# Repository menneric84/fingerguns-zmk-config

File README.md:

# v1.1
v1.1 includes support for one ALPS EC12 rotary encoder that can be placed in either the right or the left corner.  Both sockets are wired to the same pins (gpio 0 and gpio 1), so only one can be used at a time.

Pinout is identical, but the ZMK repo is not currently configured for rotary encoders.  I will dive into rotary encoders in ZMK when I have time.

Other changes: moved MCU closer to the edge, rotated hotswaps on col10 (the 11th column) to make design of the 10col case easier.

# ZMK
YOU MUST CHECK rick-plank.overlay TO ENSURE THE PROPER PHYSICAL LAYOUT IS CHOSEN

Please see the comments on line 4 of rick-plank.overlay.  In the 'chosen' node, you will need to adjust zmk,physical-layout depending on if you are using the 12 column variant or the 10 column variant of the Rick Plank PCB.

The 12 column is represented by &layout_12col
The 10 column is represented by &layout_10col

YOU MUST SELECT OR CREATE AN APPROPRIATE KEYMAP

In the ergomech community a keymap is an intensely personal thing.  That being said, I've included my own 12 column and 10 column keymaps in case you need somewhere to start.  Please note that rick-plank.keymap is intended for the 10 column variant.  A 12 column keymap is also included under the name rick-plank.keymap.12col.  If you wish to use 12 columns, simply append '.10col' to the default keymap and delete '.12col' from the other one.

# QMK?
I haven't tried it, but there's no reason it wouldn't work fine.  You'll find the pinout in the kicad schematic.  Please reach out and let me know how it goes!  If you get it up and running I'd be happy to add a QMK option to the repo.

# BOM
36-42 choc switches & keycaps  
36-42 choc hotswaps  
36-42 smd diodes  
6 M2 heat set inserts  
6 M2 x 6mm screws  
6 rubber bumpons (recommended)  
1 MSK12C02 switch  
1 Panasonic EVQPUJ_EVQPUA button  
1 pro micro form factor MCU  
1 301230 110mAh battery (optional)  

If you are confused about switches, all parts except the inserts and screws can be sourced from typeractive.xyz.

# BUILDING

If planning to use the case, the MCU should be soldered with the included headers, NOT sockets.  The sockets add too much height to fit in the case.  A hot plate is recommended for assembly, as it makes the whole process very quick and easy.  Assembly is possible by hand with a soldering iron, though it can be delicate and frustrating.  For the diodes and switches, I recommend tinning one pad first, then placing the component with tweezers before soldering the other side.  Some of the photos show a battery pigtail, but ultimately I decided to solder the battery wires directly to the board and stick the battery down with a command strip.

# CASES

Files are included to 3d print a case for the 12col variant, designed by my brother.  PCB is secured with 6 M2 heat set inserts. The 10col case is still in development, but will be added to the repo when it's done.  I've also included a .step file of the PCB under /gerbers_and_kicad if you'd like to design your own.

Rick Plank is also perfectly useable without a case if you stick a few bumpons on the hotswaps.  I placed a total of six, at the four corners and at the corners of the bottom row.

# LICENSING
All hardware in this repo is licensed under CERN-OHL-S-2.0, available at https://gitlab.com/ohwr/project/cernohl/-/wikis/uploads/819d71bea3458f71fba6cf4fb0f2de6b/cern_ohl_s_v2.txt

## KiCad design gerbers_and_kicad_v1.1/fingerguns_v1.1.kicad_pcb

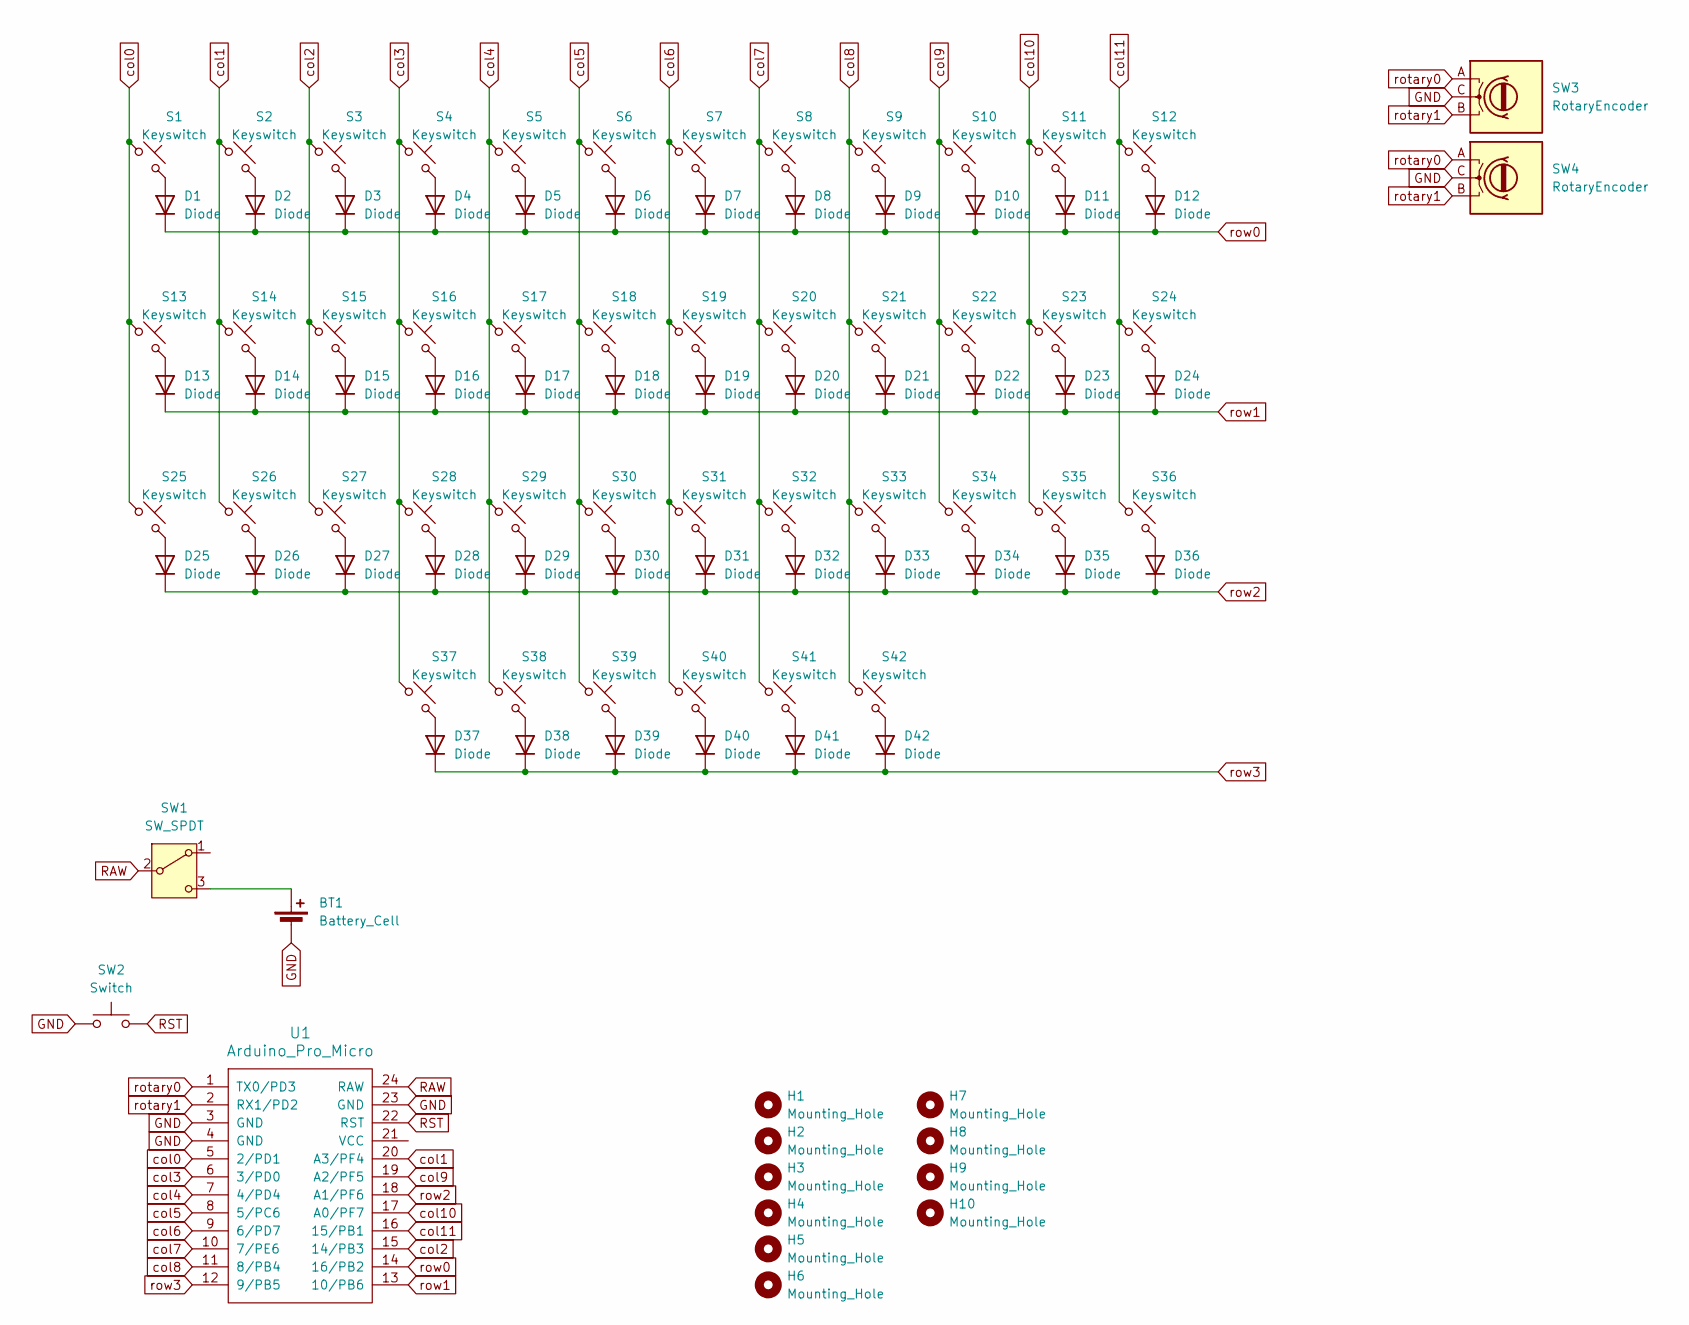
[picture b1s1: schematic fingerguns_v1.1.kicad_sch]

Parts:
BT1: Battery_Cell; Battery
D1, D2, D3, D4, D5, D6, D7, D8, D9, D10, D11, D12, D13, D14, D15, D16, D17, D18, D19, D20, D21, D22, D23, D24, D25, D26, D27, D28, D29, D30, D31, D32, D33, D34, D35, D36, D37, D38, D39, D40, D41, D42: Diode; Diode_SOD-123
H1, H2, H3, H4, H5, H6: Mounting_Hole; MountingHole_2.2mm_M2_DIN965_Pad_TopBottom
H7, H8, H9, H10: Mounting_Hole; MountingHole_3.2mm_M3
S1, S2, S3, S4, S5, S6, S7, S8, S9, S10, S11, S12, S13, S14, S15, S16, S17, S18, S19, S20, S21, S22, S23, S24, S25, S26, S27, S28, S29, S30, S31, S32, S33, S34, S35, S36, S37, S38, S39, S40, S41, S42: Keyswitch; Hotswap_Choc_V1_1.00u no silkscreen
SW1: SW_SPDT; Switch_MSK12C02
SW2: Switch; Panasonic_EVQPUJ_EVQPUA
SW3, SW4: RotaryEncoder; RotaryEncoder_Alps_EC12E_Vertical_H20mm
U1: Arduino_Pro_Micro

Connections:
GND: BT1.2 (-), SW2.1, SW3.C, SW4.C, U1.3 (GND), U1.4 (GND), U1.23 (GND)
unnamed: BT1.1 (+), SW1.3 (C)
unnamed: D1.2 (A), S1.1
unnamed: D2.2 (A), S2.1
unnamed: D3.2 (A), S3.1
unnamed: D4.2 (A), S4.1
unnamed: D5.2 (A), S5.1
unnamed: D6.2 (A), S6.1
unnamed: D7.2 (A), S7.1
unnamed: D8.2 (A), S8.1
unnamed: D9.2 (A), S9.1
unnamed: D10.2 (A), S10.1
unnamed: D11.2 (A), S11.1
unnamed: D12.2 (A), S12.1
unnamed: D13.2 (A), S13.1
unnamed: D14.2 (A), S14.1
unnamed: D15.2 (A), S15.1
unnamed: D16.2 (A), S16.1
unnamed: D17.2 (A), S17.1
unnamed: D18.2 (A), S18.1
unnamed: D19.2 (A), S19.1
unnamed: D20.2 (A), S20.1
unnamed: D21.2 (A), S21.1
unnamed: D22.2 (A), S22.1
unnamed: D23.2 (A), S23.1
unnamed: D24.2 (A), S24.1
unnamed: D25.2 (A), S25.1
unnamed: D26.2 (A), S26.1
unnamed: D27.2 (A), S27.1
unnamed: D28.2 (A), S28.1
unnamed: D29.2 (A), S29.1
unnamed: D30.2 (A), S30.1
unnamed: D31.2 (A), S31.1
unnamed: D32.2 (A), S32.1
unnamed: D33.2 (A), S33.1
unnamed: D34.2 (A), S34.1
unnamed: D35.2 (A), S35.1
unnamed: D36.2 (A), S36.1
unnamed: D37.2 (A), S37.1
unnamed: D38.2 (A), S38.1
unnamed: D39.2 (A), S39.1
unnamed: D40.2 (A), S40.1
unnamed: D41.2 (A), S41.1
unnamed: D42.2 (A), S42.1
RAW: SW1.2 (B), U1.24 (RAW)
RST: SW2.2, U1.22 (RST)
col0: S1.2, S13.2, S25.2, U1.5 (2/PD1)
col1: S2.2, S14.2, S26.2, U1.20 (A3/PF4)
col2: S3.2, S15.2, S27.2, U1.15 (14/PB3)
col3: S4.2, S16.2, S28.2, S37.2, U1.6 (3/PD0)
col4: S5.2, S17.2, S29.2, S38.2, U1.7 (4/PD4)
col5: S6.2, S18.2, S30.2, S39.2, U1.8 (5/PC6)
col6: S7.2, S19.2, S31.2, S40.2, U1.9 (6/PD7)
col7: S8.2, S20.2, S32.2, S41.2, U1.10 (7/PE6)
col8: S9.2, S21.2, S33.2, S42.2, U1.11 (8/PB4)
col9: S10.2, S22.2, S34.2, U1.19 (A2/PF5)
col10: S11.2, S23.2, S35.2, U1.17 (A0/PF7)
col11: S12.2, S24.2, S36.2, U1.16 (15/PB1)
rotary0: SW3.A, SW4.A, U1.1 (TX0/PD3)
rotary1: SW3.B, SW4.B, U1.2 (RX1/PD2)
row0: D1.1 (K), D2.1 (K), D3.1 (K), D4.1 (K), D5.1 (K), D6.1 (K), D7.1 (K), D8.1 (K), D9.1 (K), D10.1 (K), D11.1 (K), D12.1 (K), U1.14 (16/PB2)
row1: D13.1 (K), D14.1 (K), D15.1 (K), D16.1 (K), D17.1 (K), D18.1 (K), D19.1 (K), D20.1 (K), D21.1 (K), D22.1 (K), D23.1 (K), D24.1 (K), U1.13 (10/PB6)
row2: D25.1 (K), D26.1 (K), D27.1 (K), D28.1 (K), D29.1 (K), D30.1 (K), D31.1 (K), D32.1 (K), D33.1 (K), D34.1 (K), D35.1 (K), D36.1 (K), U1.18 (A1/PF6)
row3: D37.1 (K), D38.1 (K), D39.1 (K), D40.1 (K), D41.1 (K), D42.1 (K), U1.12 (9/PB5)

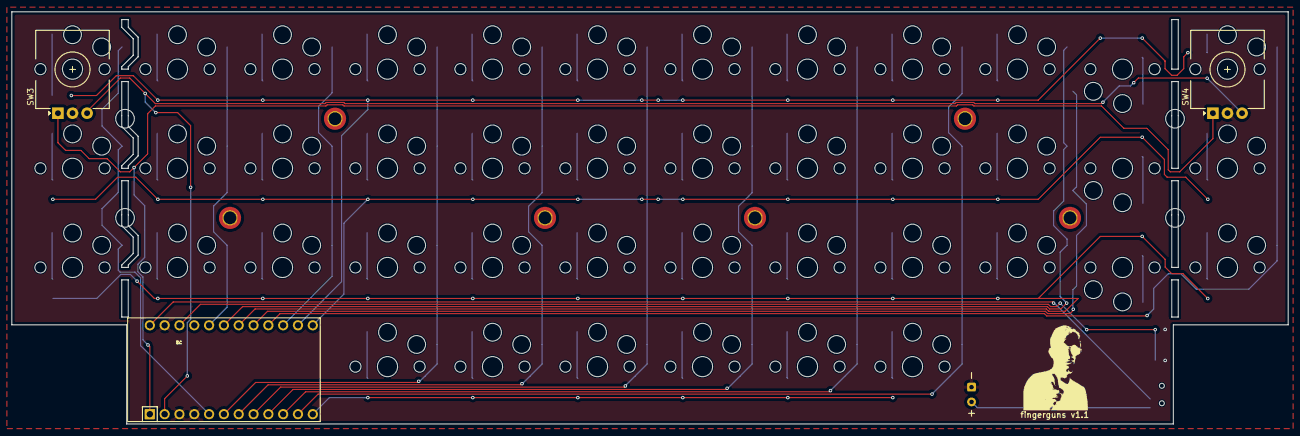
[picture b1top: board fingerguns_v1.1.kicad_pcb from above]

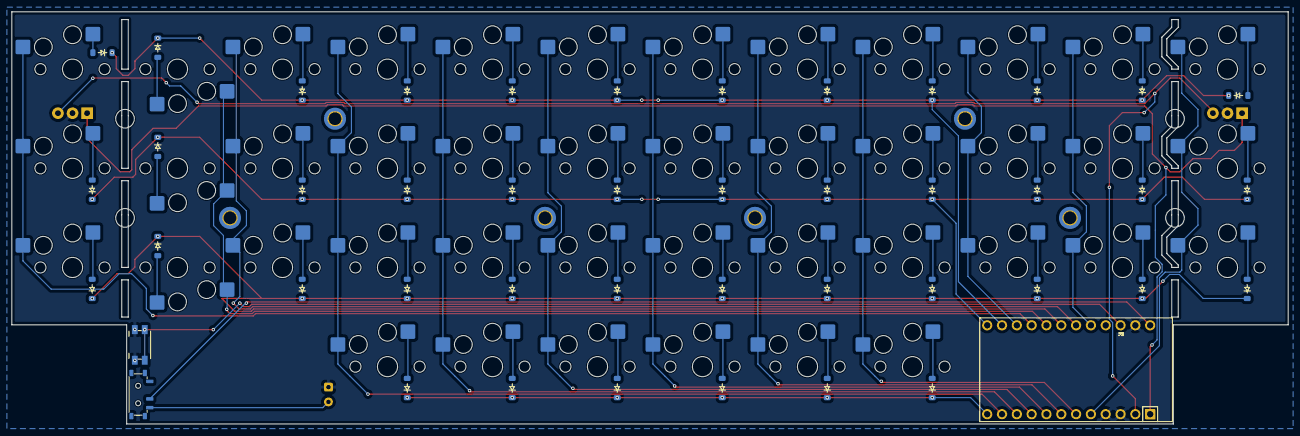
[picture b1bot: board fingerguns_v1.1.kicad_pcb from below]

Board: 2 copper layers, 218.8 x 70.7 mm, 100 parts (44 on the bottom side), 64 nets.

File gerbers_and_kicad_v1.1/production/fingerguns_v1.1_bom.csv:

"Id";"Designator";"Footprint";"Quantity";"Designation";"Supplier and ref";
1;"S2,S20,S17,S11,S19,S26,S5,S41,S33,S15,S14,S27,S35,S21,S13,S4,S1,S7,S25,S37,S32,S18,S31,S3,S40,S16,S22,S36,S10,S23,S29,S9,S34,S42,S12,S6,S39,S28,S8,S38,S30,S24";"Hotswap_Choc_V1_1.00u no silkscreen";42;"Keyswitch";;;
2;"H8,H7,H9,H10";"MountingHole_3.2mm_M3";4;"Mounting_Hole";;;
3;"H6,H1,H5,H2,H3,H4";"MountingHole_2.2mm_M2_DIN965_Pad_TopBottom";6;"Mounting_Hole";;;
4;"U1";"Arduino_Pro_Micro";1;"Arduino_Pro_Micro";;;
5;"D19,D34,D18,D22,D23,D7,D29,D41,D4,D26,D32,D25,D42,D28,D35,D40,D31,D38,D30,D12,D5,D37,D15,D2,D21,D9,D14,D33,D3,D36,D16,D1,D17,D13,D11,D27,D6,D39,D10,D20,D24,D8";"Diode_SOD-123";42;"Diode";;;
6;"SW1";"Switch_MSK12C02";1;"SW_SPDT";;;
7;"SW2";"Panasonic_EVQPUJ_EVQPUA";1;"Switch";;;
8;"BT1";"Battery";1;"Battery_Cell";;;
9;"SW4,SW3";"RotaryEncoder_Alps_EC12E_Vertical_H20mm";2;"RotaryEncoder";;;

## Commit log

2024-12-12 added Kconfig.shield, Kconfig.defconfig, fingerguns.conf
2024-12-12 Added fingerguns.overlay and README.md. NOTE: correct transform must be chosen in fingerguns.overlay
2024-12-12 Added 10col and 12col keymaps, added to README.md
2024-12-12 added fingerguns.zmk.yml
2024-12-12 Updated build.yaml and west.yml
2024-12-12 Added physical layout in fingerguns.overlay, adjusted README.md
2024-12-12 renamed transforms
2024-12-12 added display names to layouts
2024-12-12 edited layouts
2024-12-12 fixed bug on 382 in .keymap
2024-12-12 Added to README.md
2024-12-13 Changed fingerguns.overlay line 63 columns to 12
2024-12-13 added to fingerguns.overlan kscan1
2024-12-13 Separated layouts to fingerguns-layouts.dtsi, fixed col-gpio in kscan0 and kscan1
2025-08-04 Generating 12col firmware
2025-08-04 edited default bluetooth name
2025-08-05 restore to 10col variant
2025-08-05 added photos
2025-08-05 added 12col_case.3mf
2025-08-05 added gerbers and kicad files
2025-08-05 added .step file
2025-08-05 REAME.md formatting
2025-08-05 README.md formatting
2025-08-05 added pictures to README.md
2025-08-05 removed pictures
2025-08-05 added pictures
2025-10-09 uploaded v1.1 gerbers and kicad files
2025-10-26 Delete kscan1 and 12-column keymap transform
    Removed kscan1 configuration and keymap transform for 12 columns.
2025-10-26 Change kscan reference from kscan1 to kscan0
2025-10-26 Clean up fingerguns.keymap by removing comments
    Removed extensive comments and configuration for home row mods and macros.
2025-10-26 Clean up keymap configuration
    Removed commented-out keymap layers and updated bindings.
2025-10-26 Update GPIO assignments in fingerguns overlay
2025-10-26 Update GPIO pin assignments in fingerguns overlay
2025-10-26 asdf
2025-10-26 rick
2025-10-26 Revert "asdf"
    This reverts commit b54405f8777e59553b42424b7acf41fba6cd4269.
2025-10-27 Remove CONFIG_BT_RPA from rick-plank.conf
    Remove CONFIG_BT_RPA setting from rick-plank.conf
2025-10-28 Add additional GPIO and key mappings
2025-10-28 Add additional key physical attributes to layout
2025-10-28 Modify row-gpios configuration in rick-plank overlay
2025-10-28 Add GPIO and update key mapping for rick-plank
2025-10-28 Fix formatting issue in rick-plank.overlay
2025-10-28 push
2025-10-29 keymap
